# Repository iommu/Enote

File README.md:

# Enote
Eink based low power tablet

More information on my blog https://iommu.xyz

Copyright Alex Carter (iommu) 2019

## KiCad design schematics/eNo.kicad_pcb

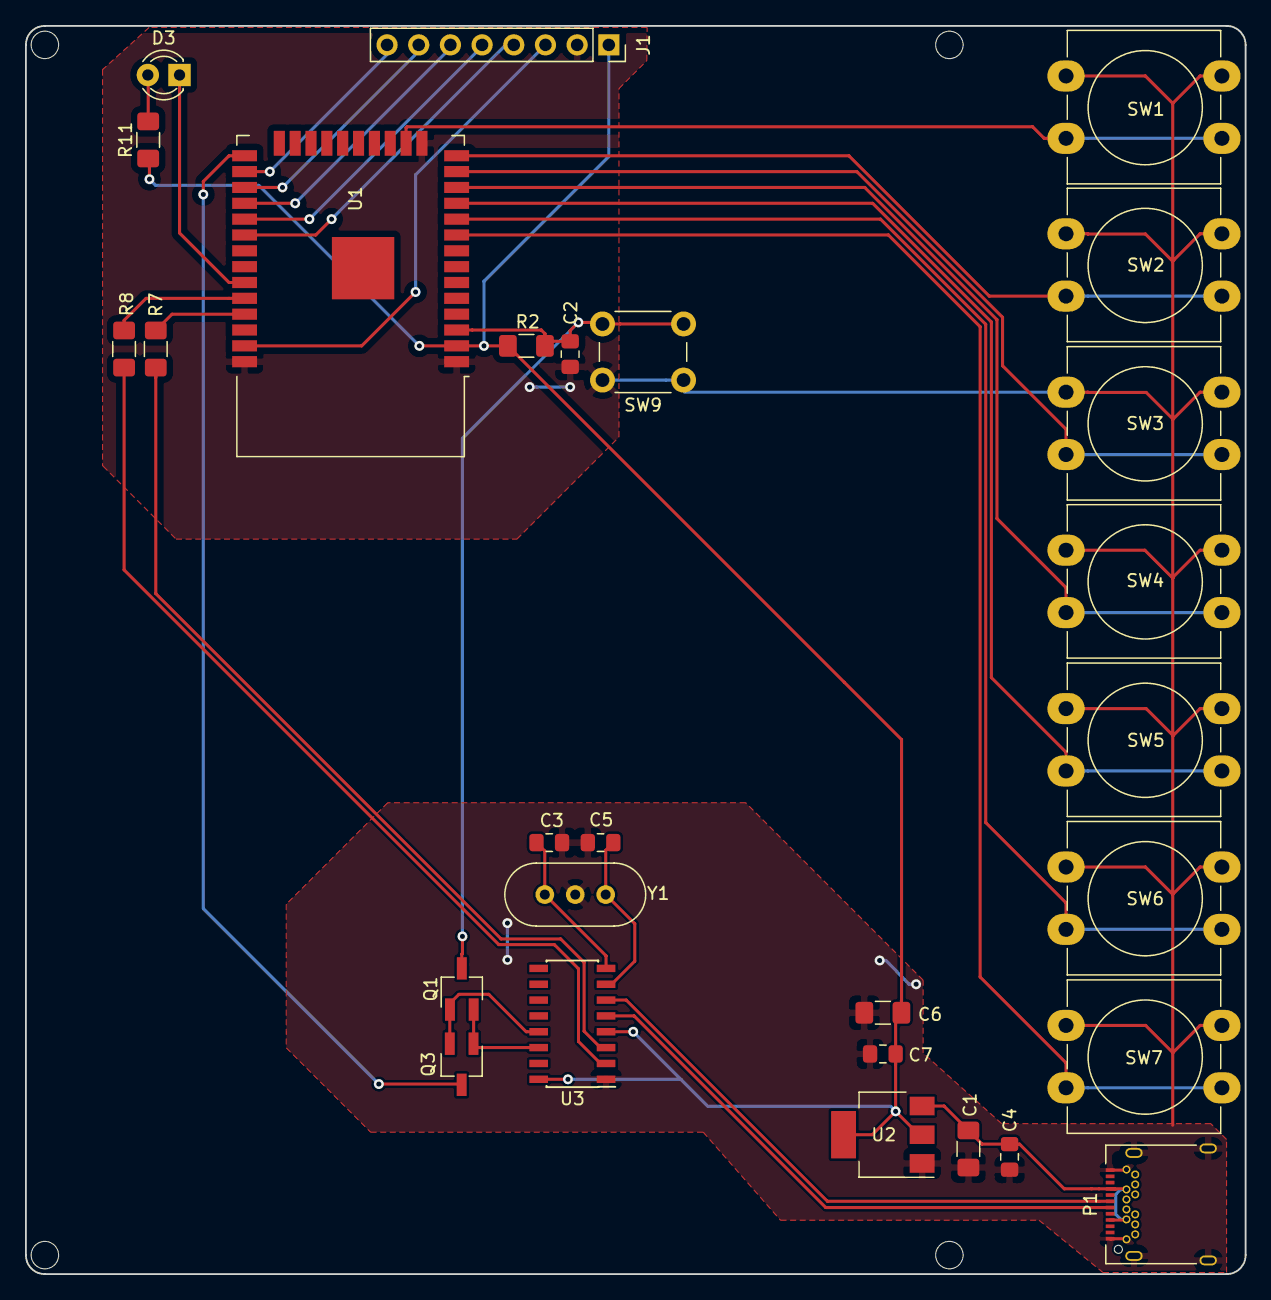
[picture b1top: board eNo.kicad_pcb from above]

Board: 2 copper layers, 97.8 x 100.1 mm, 28 parts (0 on the bottom side), 30 nets.

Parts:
C1, C6: CP; C_1206_3216Metric_Pad1.42x1.75mm_HandSolder
C2: 1uf; C_0805_2012Metric_Pad1.15x1.40mm_HandSolder
C3, C5: 22p; C_0805_2012Metric_Pad1.15x1.40mm_HandSolder
C4, C7: C; C_0805_2012Metric_Pad1.15x1.40mm_HandSolder
D3: LED; LED_D3.0mm
J1: Conn_01x08_Male; PinSocket_1x08_P2.54mm_Vertical
P1: USB_C_Plug_USB2.0; USB_C_Receptacle_Amphenol_12401548E4-2A
Q1: DTD143T; SC-59_Handsoldering
Q3: DTC143T; SC-59_Handsoldering
R2: 10k; R_1206_3216Metric_Pad1.42x1.75mm_HandSolder
R7, R8: 0; R_1206_3216Metric_Pad1.42x1.75mm_HandSolder
R11: 2k; R_1206_3216Metric_Pad1.42x1.75mm_HandSolder
SW1, SW2, SW3, SW4, SW5, SW6, SW7: SW_Push; SW_PUSH-12mm_Wuerth-430476085716
SW9: Reset; SW_PUSH_6mm
U1: ESP32-WROOM; ESP32-WROOM-32
U2: AP1117-33; SOT-223-3_TabPin2
U3: CH340G; SOIC-16_3.9x9.9mm_P1.27mm
Y1: 12Mhz; Crystal_HC49-U-3Pin_Vertical

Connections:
+3V3: C6.1, C7.1, J1.1, R2.2, R11.1, U1.2, U2.2, U3.4, U3.16
EN: C2.1, Q1.3, R2.1, SW9.2, U1.3
GND: C1.2, C2.2, C3.1, C4.2, C5.2, C6.2, C7.2, J1.2, P1.A1, P1.A12, P1.B1, P1.B12, P1.S1, SW1.1, SW2.1, SW3.1, SW4.1, SW5.1, SW6.1, SW7.1, SW9.1, U1.1, U1.15, U1.38, U2.1, U3.1, Y1.2
IO0: Q3.3, U1.25
LED: D3.1, U1.33
unnamed: D3.2, R11.2
unnamed: J1.3, U1.37
unnamed: J1.4, U1.30
unnamed: J1.5, U1.29
unnamed: J1.6, U1.28
unnamed: J1.7, U1.27
unnamed: J1.8, U1.26
unnamed: P1.A6, U3.5
unnamed: P1.A7, U3.6
unnamed: R7.1, U3.3
unnamed: R8.1, U3.2
unnamed: SW1.2, U1.16
unnamed: SW2.2, U1.14
unnamed: SW3.2, U1.13
unnamed: SW4.2, U1.12
unnamed: SW5.2, U1.11
unnamed: SW6.2, U1.10
unnamed: SW7.2, U1.9
RX: R8.2, U1.34
TX: R7.2, U1.35
VBUS: C1.1, C4.1, P1.A4, P1.A9, P1.B4, P1.B9, U2.3
XI: C5.1, U3.7, Y1.3
XO: C3.2, U3.8, Y1.1
~DTR~: Q1.1, Q3.2, U3.13
~RTS~: Q1.2, Q3.1, U3.14

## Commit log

2019-07-26 Updated readme and added first completed schematics
2019-07-27 Added epaper lib from https://github.com/mcauser/micropython-waveshare-epaper
2019-07-27 added adafruit's framebuf lib from https://github.com/adafruit/Adafruit_CircuitPython_framebuf
2019-07-27 added adafruit's font from https://github.com/adafruit/Adafruit_CircuitPython_framebuf
2019-07-28 Added epd.py from Adafruit
2019-07-28 removed SRAM
2019-07-28 converted Circuitpython to Micropython
2019-07-28 Finished conversion to micropython
2019-07-28 removed epd lib and fixed boot.py to accept adafruit frame buffer
2019-07-28 added simple model for case. (not complete)
2019-07-28 added svg from kicad
2019-07-28 added blend1 gitignore
2019-07-28 added kicad cache
